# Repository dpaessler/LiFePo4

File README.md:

# LiFePo4

Breakout for the 1A TI BQ25071 single cell LiFePo4 charger, based on the TI reference design.
Yet untested, but I'm confident :)

Board can be ordered here:

https://oshpark.com/shared_projects/dApxzwhM

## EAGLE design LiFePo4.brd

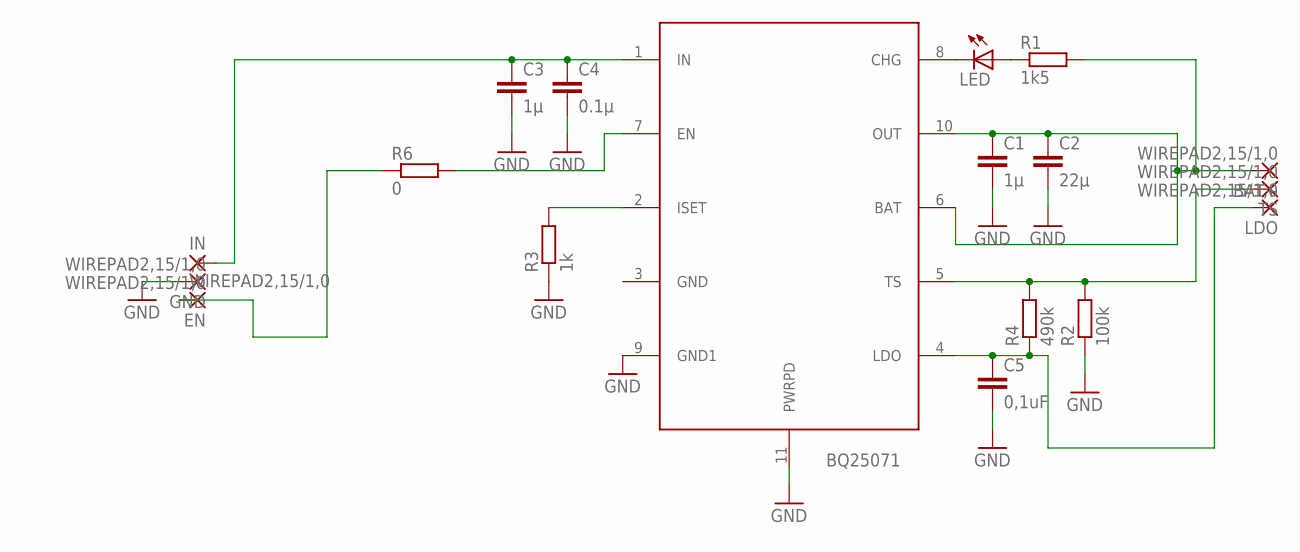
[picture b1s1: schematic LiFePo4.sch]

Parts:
BAT+: WIREPAD2,15/1,0; 2,15/1,0
BQ25071: BQ25071; WSON-10
C1, C3: 1µ; C1206
C2: 22µ; C1206
C4: 0.1µ; C1206
C5: 0,1uF; C1206
EN: WIREPAD2,15/1,0; 2,15/1,0
GND: WIREPAD2,15/1,0; 2,15/1,0
IN: WIREPAD2,15/1,0; 2,15/1,0
LDO: WIREPAD2,15/1,0; 2,15/1,0
LED: LEDSMT1206; 1206
R1: 1k5; R1206
R2: 100k; R1206
R3: 1k; R1206
R4: 490k; R1206
R6: 0; R1206
TS: WIREPAD2,15/1,0; 2,15/1,0

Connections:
BAT+: BAT+.1, BQ25071.6 (BAT), BQ25071.10 (OUT), C1.1, C2.1, R1.2
CHG: BQ25071.8 (CHG), LED.C
GROUND: BQ25071.3 (GND), BQ25071.9 (GND1), BQ25071.11 (PWRPD), C1.2, C2.2, C3.2, C4.2, C5.2, GND.1, R2.1, R3.1
LDO: BQ25071.4 (LDO), C5.1, LDO.1, R4.1
unnamed: BQ25071.7 (EN), R6.2
unnamed: LED.A, R1.1
unnamed: EN.1, R6.1
unnamed: BQ25071.2 (ISET), R3.2
unnamed: BQ25071.5 (TS), R2.2, R4.2, TS.1
unnamed: BQ25071.1 (IN), C3.1, C4.1, IN.1

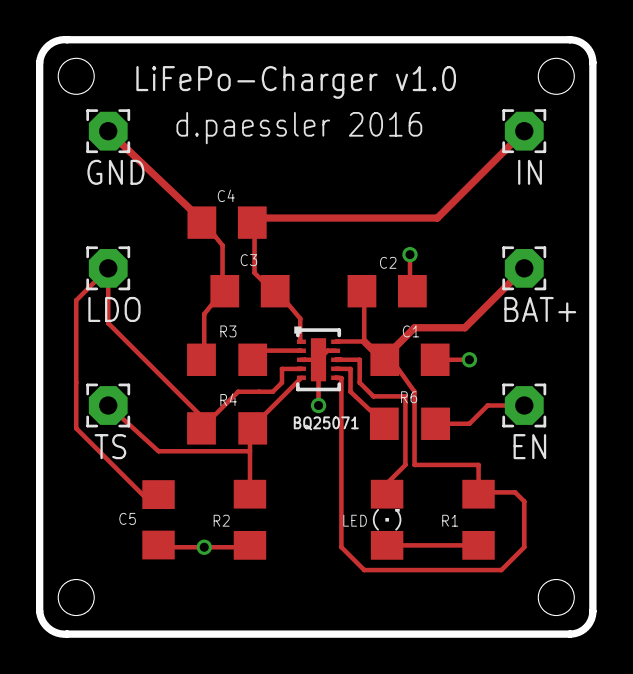
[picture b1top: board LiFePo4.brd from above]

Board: 2 copper layers, 30.7 x 33.0 mm, 18 parts (0 on the bottom side), 10 nets.

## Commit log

2016-12-04 initial release
